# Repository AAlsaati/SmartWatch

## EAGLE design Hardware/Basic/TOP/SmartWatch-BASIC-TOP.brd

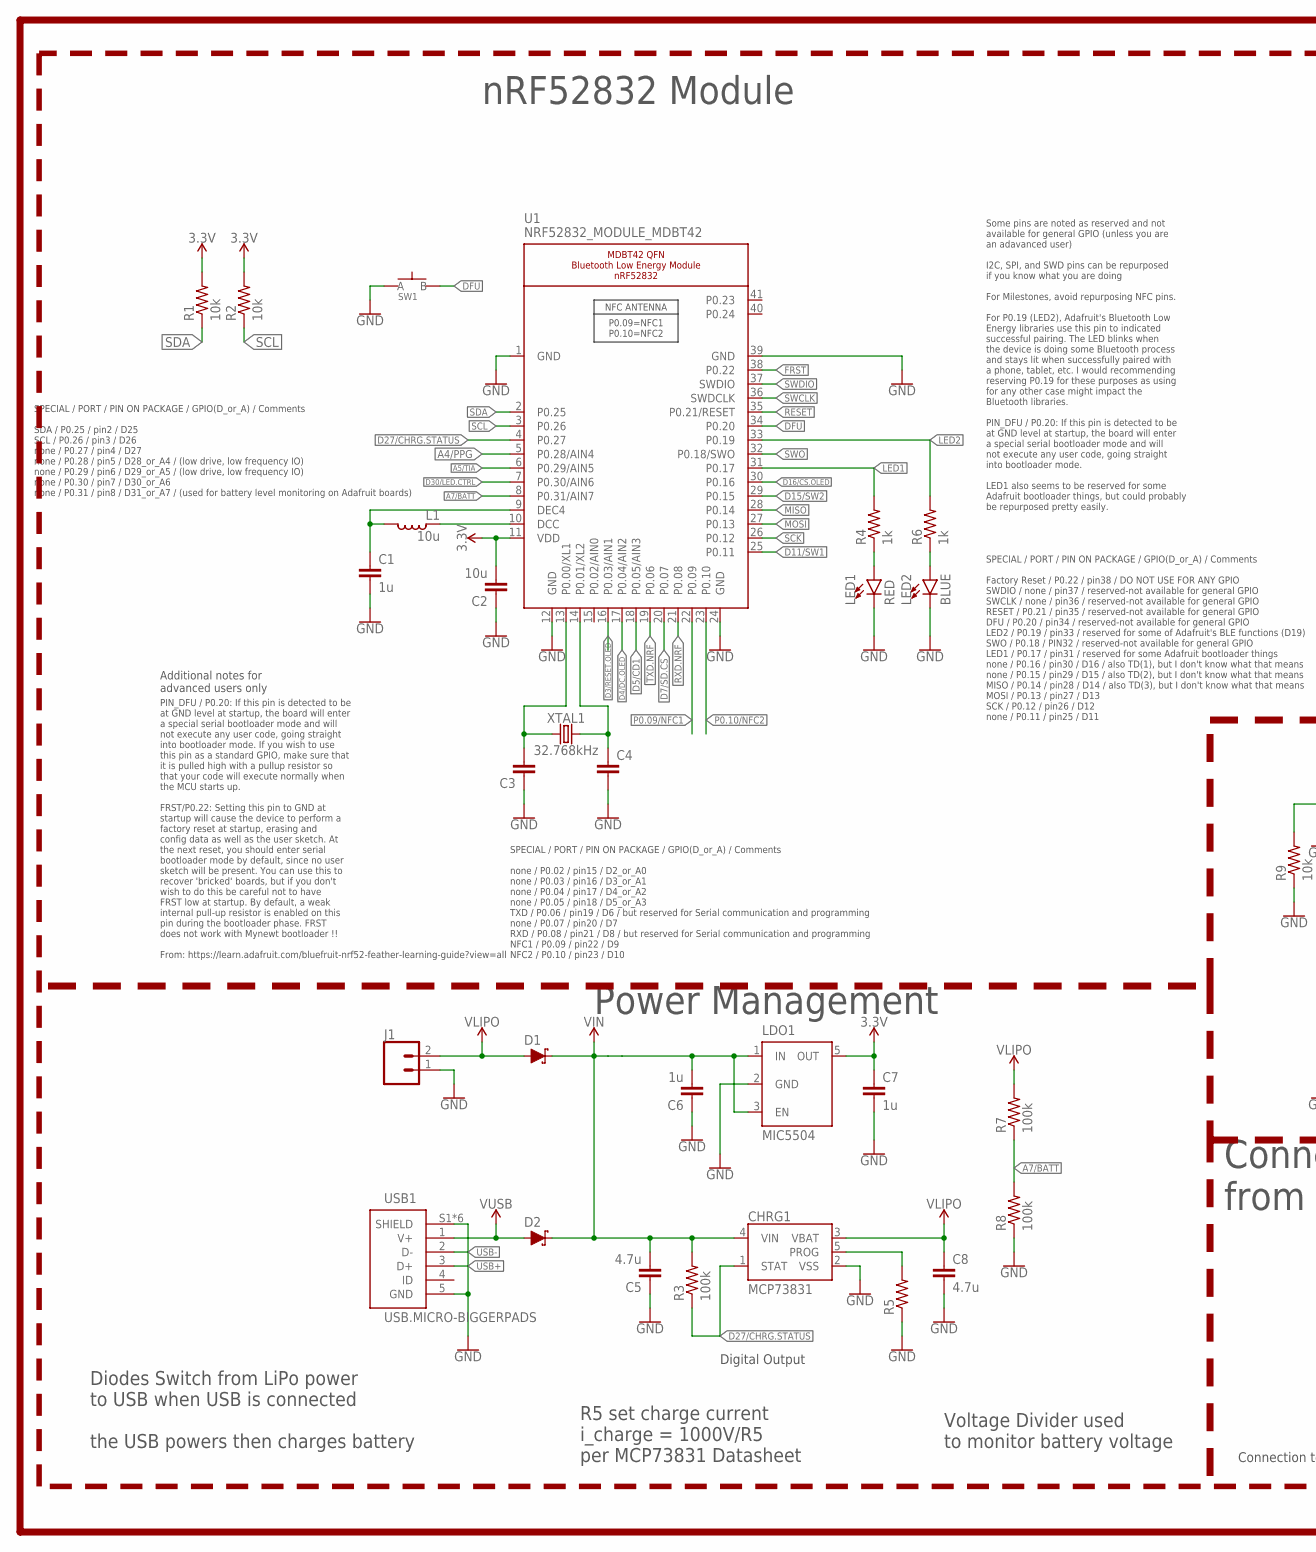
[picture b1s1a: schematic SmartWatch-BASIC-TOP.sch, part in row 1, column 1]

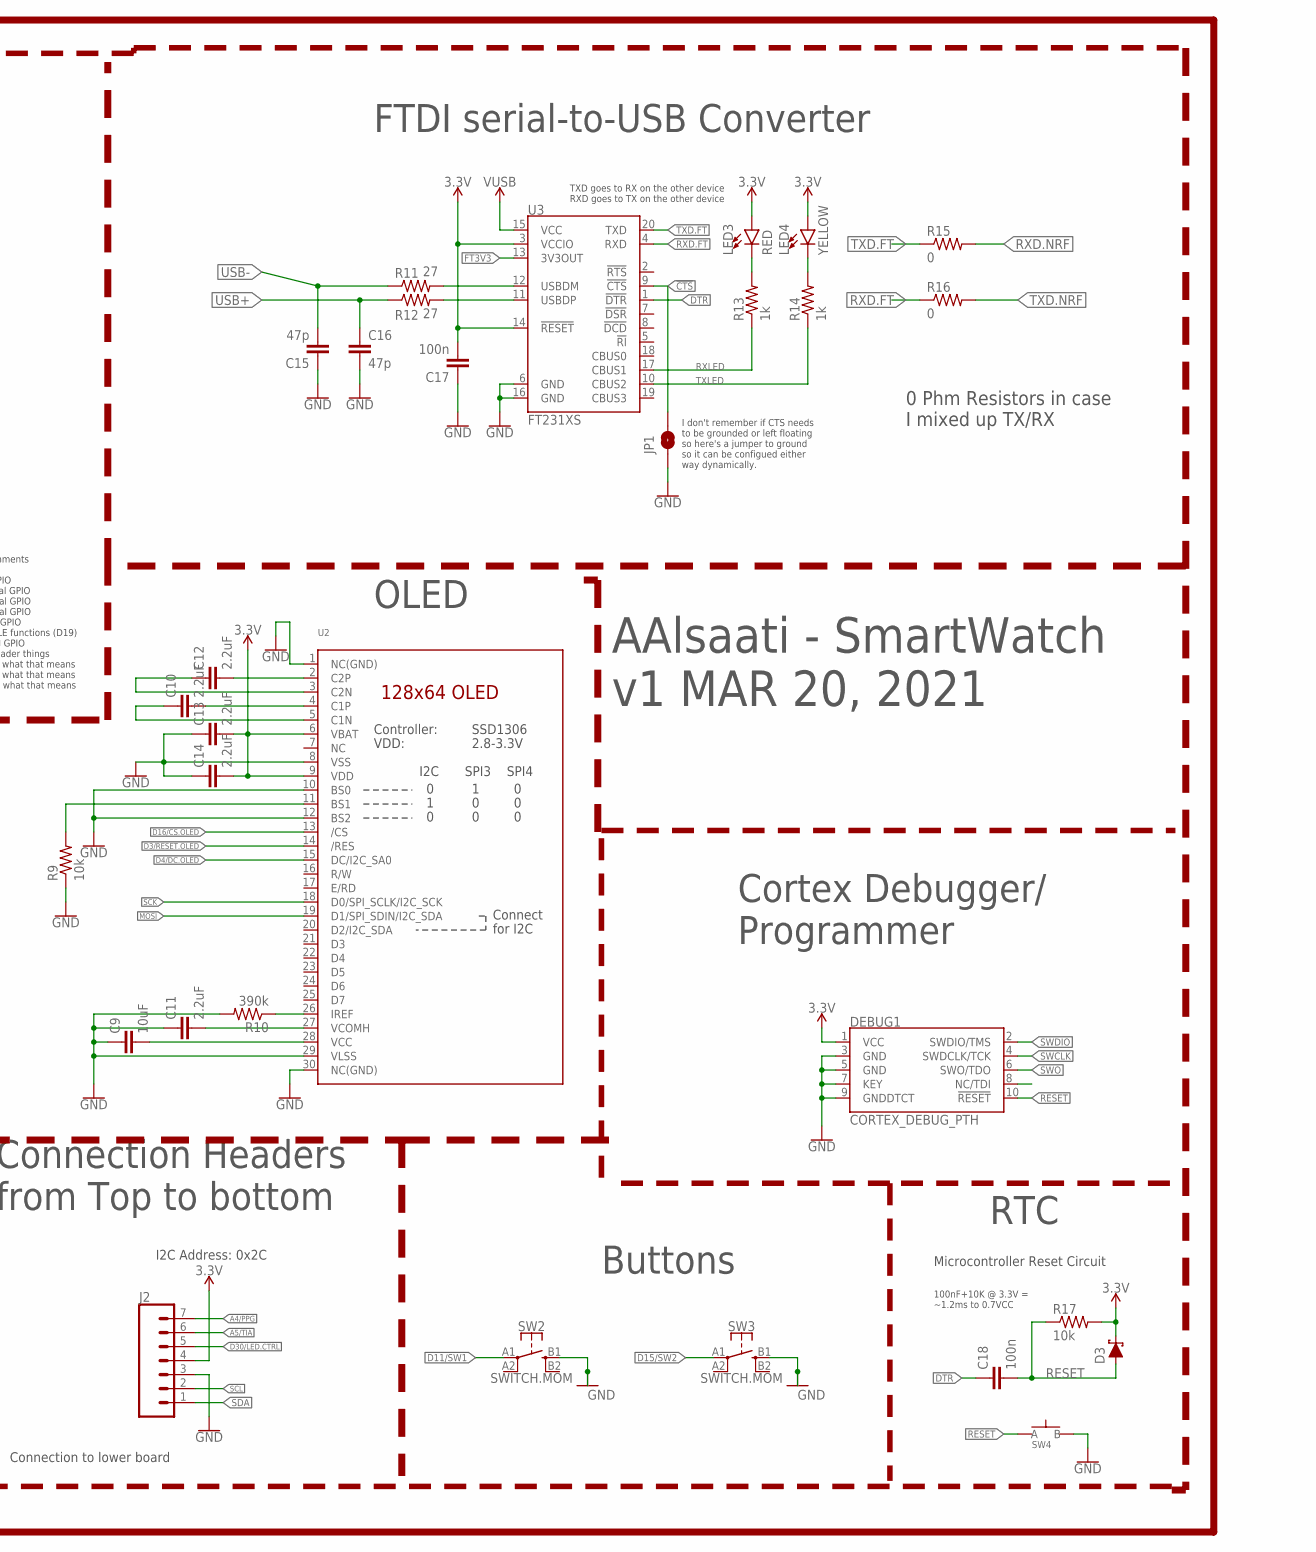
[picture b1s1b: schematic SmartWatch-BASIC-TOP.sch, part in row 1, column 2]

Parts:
C1, C6, C7: 1u; C0603
C2: 10u; C0805
C3, C4: CAPACITOR0603; C0603
C5, C8: 4.7u; C0603
C9: 10uF; C0603
C10, C12, C13, C14: 2.2uF; C0402
C11: 2.2uF; C0603
C15, C16: 47p; C0603
C17, C18: 100n; C0603
CHRG1: MCP73831; SOT23-5
D1, D2, D3: SCHOTTKY-USC; USC
DEBUG1: CORTEX_DEBUG_PTH; 2X5-PTH-1.27MM
J1: CONN_02; 1X02
J2: CONN_07-1.27MM; 1X07_1.27MM
JP1: JUMPER-SMT_2_NO_SILK; SMT-JUMPER_2_NO_SILK
L1: 10u; L0603
LDO1: MIC5504; SOT23-5
LED1, LED3: RED; LED-0603
LED2: BLUE; LED-0603
LED4: YELLOW; LED-0603
R1, R2, R9, R17: 10k; R0603
R3, R7, R8: 100k; R0603
R4, R6, R13, R14: 1k; R0603
R5: RESISTOR0603; R0603
R10: 390k; R0603
R11, R12: 27; R0603
R15, R16: 0; R0603
SW1, SW4: SPST-PTS830GG140-COPY.1-3; BUTTON-GULLWING
SW2, SW3: SWITCH.MOM; TACTILE_SWITCH_SMD_6.2MM_TALL
U1: NRF52832_MODULE_MDBT42; BLE_MODULE_RAYTAC_MDBT42
U2: DISP_OLED_UG-2864HSWEG01-NO-WRAPAROUND; UG-2864HSWEG01_0.96IN_NO-WRAPAROUND
U3: FT231XS; SSOP20_L
USB1: USB.MICRO-BIGGERPADS; USB-MICRO-01.BIGGERPADS
XTAL1: 32.768kHz; 2-SMD.NOLEAD.2.0MMTO1.2MM

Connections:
3.3V: C2.2, C7.1, C13.2, C14.2, C17.2, D3.- (C), DEBUG1.1 (VCC), J2.4, LDO1.5 (OUT), LED3.A, LED4.A, R1.2, R2.2, R17.2, U1.11 (VDD), U2.6 (VBAT), U2.9 (VDD), U3.3 (VCCIO), U3.14 (!RESET)
!CTS: JP1.2, U3.9 (!CTS)
A4/PPG: J2.7, U1.5 (P0.28/AIN4)
A5/TIA: J2.6, U1.6 (P0.29/AIN5)
A7/BATT: R7.1, R8.2, U1.8 (P0.31/AIN7)
D3/RESET.OLED: U1.16 (P0.03/AIN1), U2.14 (/RES)
D4/DC.OLED: U1.17 (P0.04/AIN2), U2.15 (DC/I2C_SA0)
D5/CD1: U1.18 (P0.05/AIN3)
D7/SD.CS: U1.20 (P0.07)
D11/SW1: SW2.A1 (1), U1.25 (P0.11)
D15/SW2: SW3.A1 (1), U1.29 (P0.15)
D16/CS.OLED: U1.30 (P0.16), U2.13 (/CS)
D27/CHRG.STATUS: CHRG1.1 (STAT), R3.1, U1.4 (P0.27)
D30/LED.CTRL: J2.5, U1.7 (P0.30/AIN6)
DFU: SW1.3 (B), U1.34 (P0.20)
DTR: C18.1, U3.1 (!DTR)
FRST: U1.38 (P0.22)
FT3V3: U3.13 (3V3OUT)
GND: C1.2, C2.1, C3.1, C4.2, C5.1, C6.1, C7.2, C8.2, C9.1, C11.1, C13.1, C14.1, C15.1, C16.2, C17.1, CHRG1.2 (VSS), DEBUG1.3 (GND), DEBUG1.5 (GND), DEBUG1.7 (KEY), DEBUG1.9 (GNDDTCT), J1.1, J2.3, JP1.1, LDO1.2 (GND), LED1.C, LED2.C, R5.1, R8.1, R9.1, R10.2, SW1.1 (A), SW2.B1 (3), SW3.B1 (3), SW4.3 (B), U1.1 (GND), U1.12 (GND), U1.24 (GND), U1.39 (GND), U2.1 (NC(GND)), U2.8 (VSS), U2.10 (BS0), U2.12 (BS2), U2.29 (VLSS), U2.30 (NC(GND)), U3.6 (GND), U3.16 (GND), USB1.5 (GND), USB1.S1 (SHIELD), USB1.S2 (SHIELD), USB1.S3 (SHIELD), USB1.S4 (SHIELD), USB1.S5 (SHIELD), USB1.S6 (SHIELD)
LED1: R4.2, U1.31 (P0.17)
LED2: R6.2, U1.33 (P0.19)
MISO: U1.28 (P0.14)
MOSI: U1.27 (P0.13), U2.19 (D1/SPI_SDIN/I2C_SDA)
unnamed: R9.2, U2.11 (BS1)
unnamed: R10.1, U2.26 (IREF)
unnamed: C12.2, U2.2 (C2P)
unnamed: C3.2, U1.13 (P0.00/XL1), XTAL1.P$1 (1)
unnamed: C12.1, U2.3 (C2N)
unnamed: C4.1, U1.14 (P0.01/XL2), XTAL1.P$2 (2)
unnamed: C10.2, U2.4 (C1P)
unnamed: C10.1, U2.5 (C1N)
unnamed: LED1.A, R4.1
unnamed: LED2.A, R6.1
unnamed: L1.1, U1.10 (DCC)
unnamed: C1.1, L1.2, U1.9 (DEC4)
unnamed: C9.2, U2.28 (VCC)
unnamed: C11.2, U2.27 (VCOMH)
unnamed: CHRG1.5 (PROG), R5.2
unnamed: R11.2, U3.12 (USBDM)
unnamed: R12.2, U3.11 (USBDP)
unnamed: LED3.C, R13.2
unnamed: LED4.C, R14.2
P0.09/NFC1: U1.22 (P0.09)
P0.10/NFC2: U1.23 (P0.10)
RESET: C18.2, D3.+ (A), DEBUG1.10 (!RESET), R17.1, SW4.1 (A), U1.35 (P0.21/RESET)
RXD.FT: R16.1, U3.4 (RXD)
RXD.NRF: R15.2, U1.21 (P0.08)
RXLED: R13.1, U3.17 (CBUS1)
SCK: U1.26 (P0.12), U2.18 (D0/SPI_SCLK/I2C_SCK)
SCL: J2.2, R2.1, U1.3 (P0.26)
SDA: J2.1, R1.1, U1.2 (P0.25)
SWCLK: DEBUG1.4 (SWDCLK/TCK), U1.36 (SWDCLK)
SWDIO: DEBUG1.2 (SWDIO/TMS), U1.37 (SWDIO)
SWO: DEBUG1.6 (SWO/TDO), U1.32 (P0.18/SWO)
TXD.FT: R15.1, U3.20 (TXD)
TXD.NRF: R16.2, U1.19 (P0.06)
TXLED: R14.1, U3.10 (CBUS2)
USB+: C16.1, R12.1, USB1.3 (D+)
USB-: C15.2, R11.1, USB1.2 (D-)
VIN: C5.2, C6.2, CHRG1.4 (VIN), D1.- (C), D2.- (C), LDO1.1 (IN), LDO1.3 (EN), R3.2
VLIPO: C8.1, CHRG1.3 (VBAT), D1.+ (A), J1.2, R7.2
V_USB: D2.+ (A), U3.15 (VCC), USB1.1 (V+)

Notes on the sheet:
Microcontroller Reset Circuit
100nF+10K @ 3.3V = ~1.2ms to 0.7VCC
SPECIAL / PORT / PIN ON PACKAGE / GPIO(D_or_A) / Comments SDA / P0.25 / pin2 / D25 SCL / P0.26 / pin3 / D26 none / P0.27 / pin4 / D27 none / P0.28 / pin5 / D28_or_A4 / (low drive, low frequency IO) none / P0.29 / pin6 / D29_or_A5 / (low drive, low frequency IO) none / P0.30 / pin7 / D30_or_A6 none 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
SPECIAL / PORT / PIN ON PACKAGE / GPIO(D_or_A) / Comments none / P0.02 / pin15 / D2_or_A0 none / P0.03 / pin16 / D3_or_A1 none / P0.04 / pin17 / D4_or_A2 none / P0.05 / pin18 / D5_or_A3 TXD / P0.06 / pin19 / D6 / but reserved for Serial communication and programming none / P0.07 / pin20 / D7 RXD / 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
SPECIAL / PORT / PIN ON PACKAGE / GPIO(D_or_A) / Comments Factory Reset / P0.22 / pin38 / DO NOT USE FOR ANY GPIO SWDIO / none / pin37 / reserved-not available for general GPIO SWCLK / none / pin36 / reserved-not available for general GPIO RESET / P0.21 / pin35 / reserved-not available for general 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
Some pins are noted as reserved and not available for general GPIO (unless you are an adavanced user) I2C, SPI, and SWD pins can be repurposed if you know what you are doing For Milestones, avoid repurposing NFC pins. For P0.19 (LED2), Adafruit's Bluetooth Low Energy libraries use this pin to indic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
PIN_DFU / P0.20: If this pin is detected to be at GND level at startup, the board will enter a special serial bootloader mode and will not execute any user code, going straight into bootloader mode. If you wish to use this pin as a standard GPIO, make sure that it is pulled high with a pullup resis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
Additional notes for advanced users only
nRF52832 Module
OLED
Power Management
Buttons
Cortex Debugger/ Programmer
RTC
TXD goes to RX on the other device RXD goes to TX on the other device
I don't remember if CTS needs to be grounded or left floating so here's a jumper to ground so it can be configued either way dynamically.
FTDI serial-to-USB Converter
I2C Address: 0x2C
Connection to lower board
Digital Output
AAlsaati - SmartWatch v1 MAR 20, 2021
Diodes Switch from LiPo power to USB when USB is connected the USB powers then charges battery
R5 set charge current i_charge = 1000V/R5 per MCP73831 Datasheet
Voltage Divider used to monitor battery voltage
Connection Headers from Top to bottom
0 Phm Resistors in case I mixed up TX/RX

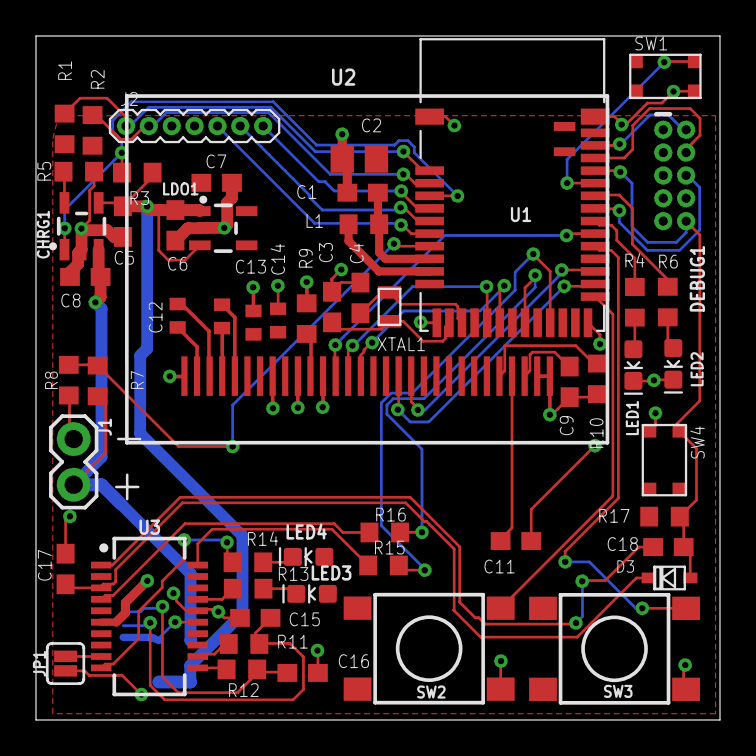
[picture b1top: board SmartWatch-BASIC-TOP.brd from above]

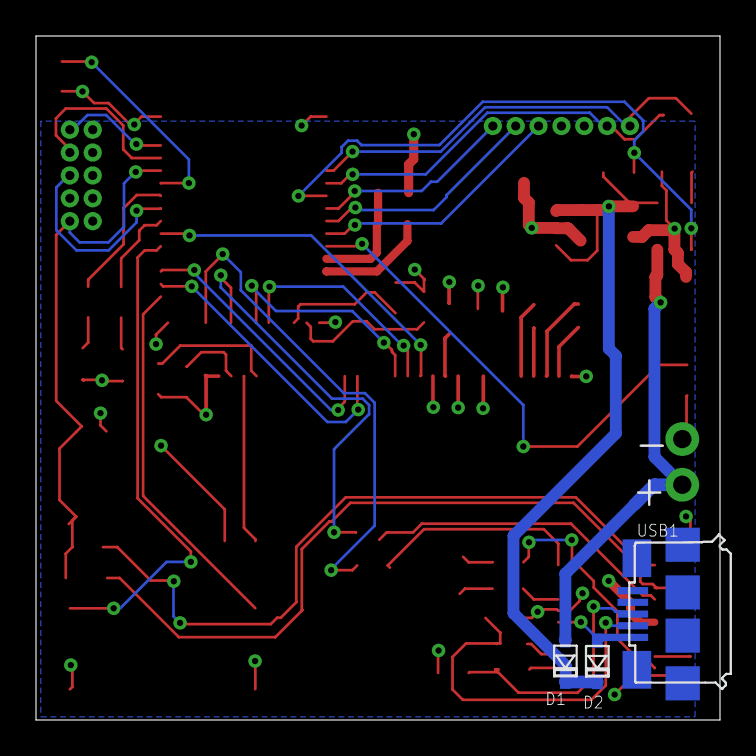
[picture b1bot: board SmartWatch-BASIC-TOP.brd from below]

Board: 2 copper layers, 38.0 x 38.0 mm, 58 parts (3 on the bottom side), 55 nets.

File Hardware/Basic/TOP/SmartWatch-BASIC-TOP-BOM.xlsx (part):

Design Name -- Revision Code / Designer or Organization Name |  |  |  |  |  |  |  |  |  |  | Total | 24.099299999999999 | Total (in Bulk) | 0
BOM # | Comment | Designator | Description | Mounting Type | Package | Manufacturer | Manufacturer Part Number | Supplier | Supplier Part Number | Price per unit | Quantity | Total | Per 100 | Total
Microcontroller
1 | NRF52832_MODULE_MDBT42 | U1 | Bluetooth Bluetooth v4.2 Transceiver Module 2.4GHz Integrated, Chip Surface Mou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 | SMD | 41-SMD Module | Seeed Technology Co., Ltd | 317030213 | Digi-Key | 1597-1434-ND | 10.1 | 1 | 10.1
2 | 10k Resistor | R1, R2, | 10 kOhms ±1% 0.1W, 1/10W Chip Resistor 0603 (1608 Metric) Automotive AEC-Q200 T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 | SMD | 0603 | Stackpole Electronics Inc | RMCF0603FT10K0 | Digi-Key | RMCF0603FT10K0CT-ND | 5.8999999999999999E-3 | 2 | 1.18E-2
3 | 1k Resistor | R4,R6 | 1 kOhms ±1% 0.1W, 1/10W Chip Resistor 0603 (1608 Metric) Automotive AEC-Q200 Th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 | SMD | 0603 | Stackpole Electronics Inc | RMCF0603FT1K00 | Digi-Key | RMCF0603FT1K00CT-ND | 5.8999999999999999E-3 | 2 | 1.18E-2
4 | Tiny Rectangular Switch | SW4 | Tactile Switch SPST-NO Top Actuated Surface Mount | SMD | Gull Wing | C&K Components | PTS830GM140 SMTR LFS | Digi-Key | CKN10587CT-ND | 0.56999999999999995 | 1 | 0.56999999999999995
5 | 10µH Inductor | L1 | 10µH Shielded Multilayer Inductor 250mA 1.05Ohm 0603 (1608 Metric) | SMD | 0603 | TDK Corporation | MLZ1608M100WTD25 | Digi-Key | MLZ1608M100WTD25 | 0.22 | 1 | 0.22
6 | 1uF capacitor | C1 | 1µF ±10% 25V Ceramic Capacitor X5R 0603 (1608 Metric) | SMD | 0603 | Samsung Electro-Mechanics | CL10A105KA8NNNC | Digi-Key | 1276-1102-1-ND | 0.1 | 1 | 0.1
7 | 10 uF 0603 Capacitor | C2 | 10µF ±10% 10V Ceramic Capacitor X5R 0603 (1608 Metric) | SMD | 0603 | Murata Electronics | GRM188R61A106KE69J | Digi-Key | 490-14372-1-ND | 6.3200000000000006E-2 | 1 | 6.3200000000000006E-2
8 | 12pF capacitor | C3, C4 | 12pF ±5% 50V Ceramic Capacitor C0G, NP0 0603 (1608 Metric) | SMD | 0603 | Walsin Technology Corporation | 0603N120J500CT | Digi-Key | 1292-1480-1-ND | 1.1900000000000001E-2 | 2 | 2.3800000000000002E-2
9 | Red LED | LED1 | Red 622nm LED Indication - Discrete 2.2V 0603 (1608 Metric) | SMD | 0603 | Inolux | IN-S63ATR | Digi-Key | 1830-1065-1-ND | 0.17699999999999999 | 1 | 0.17699999999999999
10 | Blue LED | LED2 | Blue 470nm LED Indication - Discrete 3V 0603 (1608 Metric) | SMD | 0603 | Inolux | IN-S63AT5B | Digi-Key | 1830-1061-1-ND | 0.17699999999999999 | 1 | 0.17699999999999999
11 | CRYSTALECS-.327-12.5-12-C-TR (CRYSTAL) (32.7680kHz) | XTAL1 | 32.768kHz ±10ppm Crystal 12.5pF 90 kOhms 2-SMD, No Lead | SMD | 2-SMD, No Lead | ECS Inc. | ECS-.327-12.5-12-C-TR | Digi-Key | XC2288CT-ND | 0.59799999999999998 | 1 | 0.59799999999999998
FTDI - USB |  |  |  |  |  |  |  |  |  |  |  | 0
12 | FT231XS USB Serial | U3 | USB Bridge, USB to UART USB 2.0 UART Interface 20-SSOP | SMD | 20-SSOP | FTDI, Future Technology Devices International Ltd | FT231XS-U | Digi-Key | 768-1156-5-ND | 2.12 | 1 | 2.12
13 | 47 pF Capacitor | C15, C16 | 47pF ±5% 50V Ceramic Capacitor C0G, NP0 0603 (1608 Metric) | SMD | 0603 | Walsin Technology Corporation | 0603N470J500CT | Digi-Key | 1292-1528-1-ND | 1.0999999999999999E-2 | 2 | 2.1999999999999999E-2
14 | 27 ohm resistor | R11, R12 | 27 Ohms ±1% 0.1W, 1/10W Chip Resistor 0603 (1608 Metric) Automotive AEC-Q200 Th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 | SMD | 0603 | Stackpole Electronics Inc | RMCF0603FT27R0 | Digi-Key | RMCF0603FT27R0CT-ND | 5.8999999999999999E-3 | 2 | 1.18E-2
15 | 100 nF Capacitor | C17 | 0.1µF ±5% 16V Ceramic Capacitor X7R 0603 (1608 Metric) | SMD | 0603 | Yageo | CC0603JRX7R7BB104 | Digi-Key | 311-1776-1-ND | 3.3099999999999997E-2 | 1 | 3.3099999999999997E-2
16 | 0 ohm resistor (not sure if needed) | JP1, R15, R16 | 0 Ohms Jumper 0.1W, 1/10W Chip Resistor 0603 (1608 Metric) Moisture Resistant T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 | SMD | 0603 | Yageo | RC0603JR-070RL | Digi-Key | 311-0.0GRCT-ND | 7.0000000000000001E-3 | 3 | 2.1000000000000001E-2
17 | 1k Resistor | R13,R14 | 1 kOhms ±1% 0.1W, 1/10W Chip Resistor 0603 (1608 Metric) Automotive AEC-Q200 Th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 | SMD | 0603 | Stackpole Electronics Inc | RMCF0603FT1K00 | Digi-Key | RMCF0603FT1K00CT-ND | 5.8999999999999999E-3 | 2 | 1.18E-2
18 | Red LED | LED3 | Red 622nm LED Indication - Discrete 2.2V 0603 (1608 Metric) | SMD | 0603 | Inolux | IN-S63ATR | Digi-Key | 1830-1065-1-ND | 0.17699999999999999 | 1 | 0.17699999999999999
19 | Yellow LED | LED4 | Yellow 590nm LED Indication - Discrete 2V 0603 (1608 Metric) | SMD | 0603 | Wurth Electronics Inc. | 150060YS75000 | Digi-Key | 732-4981-1-ND | 0.14000000000000001 | 1 | 0.14000000000000001
Debug |  |  |  |  |  |  |  |  |  |  |  | 0
20 | Cortex Debug Connector - 10 pin | DEBUG1 | Connector Header Through Hole 10 position 0.050" (1.27mm) | THT | NA | Amphenol ICC (FCI) | 20021111-00010T4LF | Digi-Key | 609-3712-ND | 0.69 | 1 | 0.69
RTC |  |  |  |  |  |  |  |  |  |  |  | 0
21 | 100 nF Capacitor | C18 | 0.1µF ±5% 16V Ceramic Capacitor X7R 0603 (1608 Metric) | SMD | 0603 | Yageo | CC0603JRX7R7BB104 | Digi-Key | 311-1776-1-ND | 3.3099999999999997E-2 | 1 | 3.3099999999999997E-2
22 | 10k Resistor | R17 | 10 kOhms ±1% 0.1W, 1/10W Chip Resistor 0603 (1608 Metric) Automotive AEC-Q200 T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 | SMD | 0603 | Stackpole Electronics Inc | RMCF0603FT10K0 | Digi-Key | RMCF0603FT10K0CT-ND | 5.8999999999999999E-3 | 1 | 5.8999999999999999E-3
23 | Schottky Diode | D3 | Diode Schottky 30V 1.5A Surface Mount USC | SMD | USC | Toshiba Semiconductor and Storage | CUS15S30,H3F | Digi-Key | CUS15S30H3FCT-ND | 0.25600000000000001 | 1 | 0.25600000000000001
24 | Tiny Rectangular Switch | SW4 | Tactile Switch SPST-NO Top Actuated Surface Mount | SMD | Gull Wing | C&K Components | PTS830GM140 SMTR LFS | Digi-Key | CKN10587CT-ND | 0.56999999999999995 | 1 | 0.56999999999999995
OLED |  |  |  |  |  |  |  |  |  |  |  | 0
25 | 0.96" OLED | OLED | Datasheet 128x64 OLED Module SPI 0.96"Graphic Displays,White on Black | SMD | Flexible Connector | EastRising | https://www.buydisplay.com/datasheet-128x64-oled-module-spi-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 | BuyDisplay.com | https://www.buydisplay.com/datasheet-128x64-oled-module-spi-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 | 2.5099999999999998 | 1 | 2.5099999999999998
26 | 10 uF 0603 Capacitor | C9 | 10µF ±10% 10V Ceramic Capacitor X5R 0603 (1608 Metric) | SMD | 0603 | Murata Electronics | GRM188R61A106KE69J | Digi-Key | 490-14372-1-ND | 6.3200000000000006E-2 |  | 0
27 | 2.2u capacitor | C10, C11, C12, C13, C14 | 2.2µF ±10% 16V Ceramic Capacitor X5R 0603 (1608 Metric) | SMD | 0603 | Samsung Electro-Mechanics | CL10A225KO8NNNC | Digi-Key | 1276-1040-1-ND | 3.1600000000000003E-2 | 5 | 0.15800000000000003
28 | 10k Resistor | R9 | 10 kOhms ±1% 0.1W, 1/10W Chip Resistor 0603 (1608 Metric) Automotive AEC-Q200 T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 | SMD | 0603 | Stackpole Electronics Inc | RMCF0603FT10K0 | Digi-Key | RMCF0603FT10K0CT-ND | 5.8999999999999999E-3 | 1 | 5.8999999999999999E-3
29 | 390k resistor | R10 | 390 kOhms ±1% 0.1W, 1/10W Chip Resistor 0603 (1608 Metric) Automotive AEC-Q200 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 | SMD | 0603 | Stackpole Electronics Inc | RMCF0603FG390K | Digi-Key | RMCF0603FG390KCT-ND | 5.8999999999999999E-3 | 1 | 5.8999999999999999E-3
Bottons |  |  |  |  |  |  |  |  |  |  |  | 0
30 | SWITCH.MOM (TACTILE_SWITCH_SMD_6.2MM_TALL) | SW2, SW3 | Tactile Switch SPST-NO Top Actuated Surface Mount - TACT 4.5 X 4.5, 5.0 MM H, 1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 | SMD | Gull Wing | C&K | PTS 647 SN50 SMTR2 LFS | Digi-Key | PTS647SN50SMTR2LFSCT-ND | 0.1208 | 2 | 0.24160000000000001
Connectors |  |  |  |  |  |  |  |  |  |  |  | 0
31 | CONN_07-1.27MM | J2 | 50 Positions Header Connector 0.050" (1.27mm) Through Hole Gold | THT |  | Sullins Connector Solutions | GRPB501VWVN-RC | Digi-Key | S9014E-50-ND | 3.11 | 1 | 3.11
Power |  |  |  |  |  |  |  |  |  |  |  | 0
32 | Micro USB | USB1 | USB - micro B USB 2.0 Receptacle Connector 5 Position Surface Mount, Right Angle | SMD | Flange, Horizontal | Amphenol FCI | 10118192-0001LF | Digi-Key | 609-4613-1-ND | 0.43 | 1 | 0.43
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
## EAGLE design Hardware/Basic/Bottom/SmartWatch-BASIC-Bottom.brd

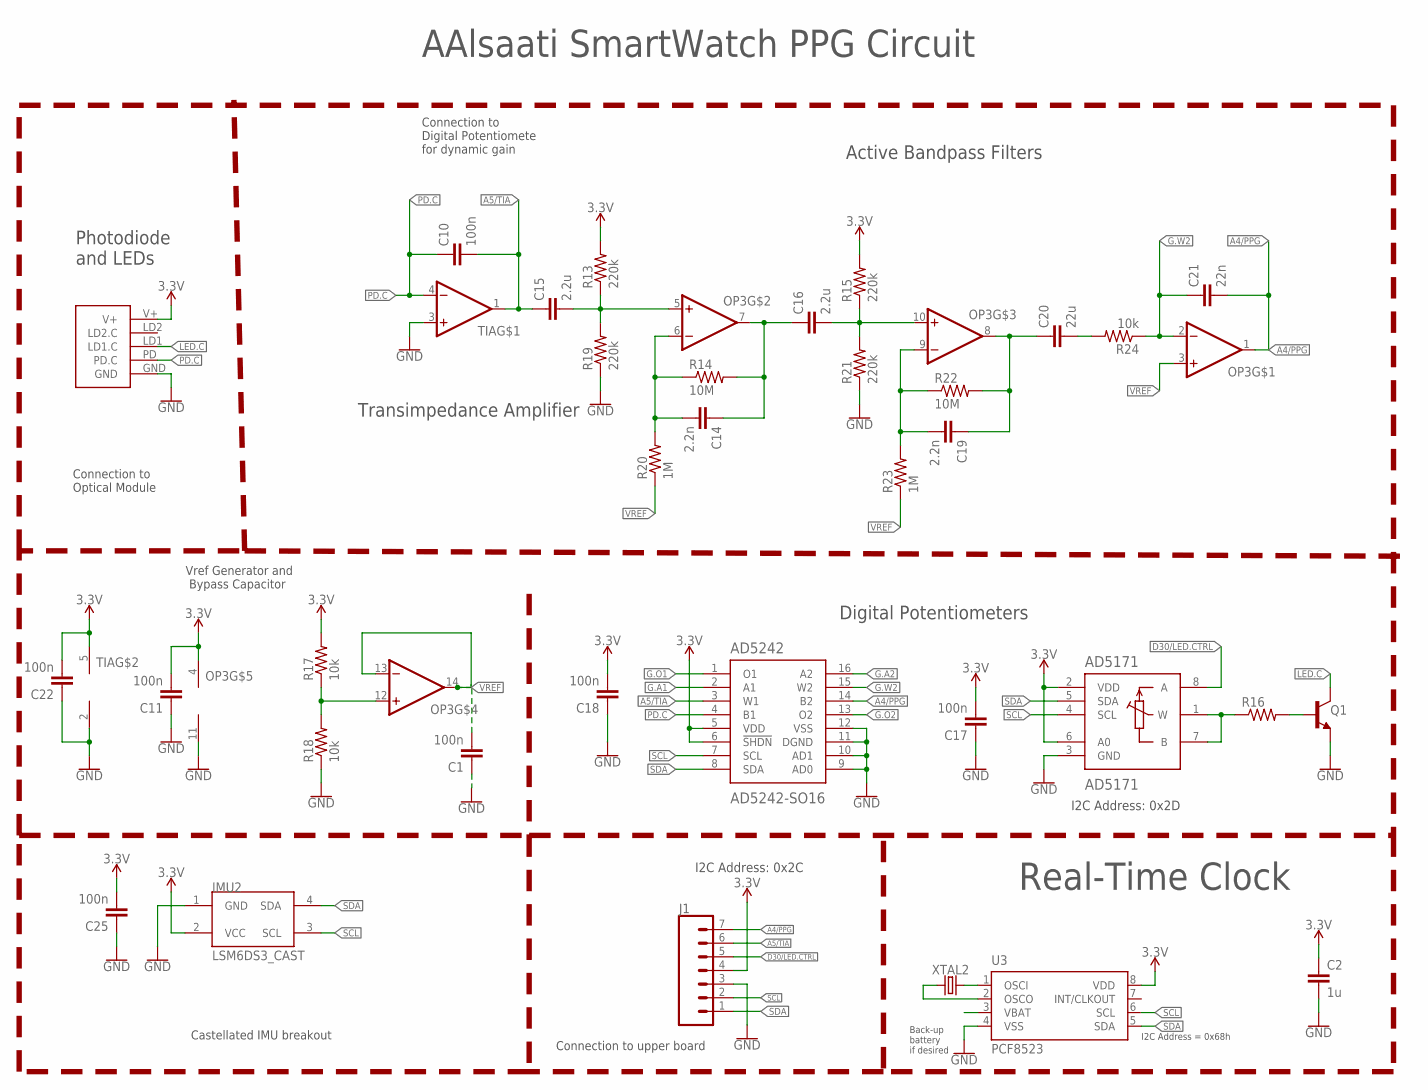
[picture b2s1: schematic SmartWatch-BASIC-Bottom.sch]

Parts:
AD5171: AD5171; SOT-23-8
AD5242: AD5242-SO16; SO16
C1, C10, C11, C17, C18, C22, C25: 100n; C0603
C2: 1u; C0603
C14, C19: 2.2n; C0603
C15, C16: 2.2u; C0603
C20: 22u; C0603
C21: 22n; C0603
IMU2: LSM6DS3_CAST
J1: CONN_07-1.27MM; 1X07_1.27MM
LOGO1: REVISION.A; REV.A
OP3: OP-QUAD-SO14; SO14
Q1: NPN-GENERIC; SOT23-3
R13, R15, R19, R21: 220k; R0603
R14, R22: 10M; R0603
R16: RESISTOR0603; R0603
R17, R18: 10k; R0402
R20, R23: 1M; R0603
R24: 10k; R0603
TIA: OP-SINGLEOT; SOT23-5
U3: PCF8523; SO8; DIGIKEY 568-5306-1-ND
U$3: PPG.MODULE.2
XTAL2: 32.7680kHz; 2-SMD.NOLEAD.2.0MMTO1.2MM

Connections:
3.3V: AD5171.2 (VDD), AD5171.6 (A0), AD5242.5 (VDD), AD5242.6 (!SHDN), C2.1, C11.2, C17.2, C18.2, C22.2, C25.2, IMU2.2 (VCC), J1.4, OP3.4 (V+), R13.2, R15.2, R17.2, TIA.5 (V+), U3.8 (VDD), U$3.V+
A4/PPG: AD5242.14 (B2), C21.2, J1.7, OP3.1 (OUT)
A5/TIA: AD5242.3 (W1), C10.2, C15.1, J1.6, TIA.1 (OUT)
D30/LED.CTRL: AD5171.8 (A), J1.5
G.A1: AD5242.2 (A1)
G.A2: AD5242.16 (A2)
G.O1: AD5242.1 (O1)
G.O2: AD5242.13 (O2)
G.W2: AD5242.15 (W2), C21.1, OP3.2 (-IN), R24.1
GND: AD5171.3 (GND), AD5242.9 (AD0), AD5242.10 (AD1), AD5242.11 (DGND), AD5242.12 (VSS), C1.1, C2.2, C11.1, C17.1, C18.1, C22.1, C25.1, IMU2.1 (GND), J1.3, OP3.11 (V-), Q1.2 (E), R18.1, R19.1, R21.1, TIA.2 (V-), TIA.3 (+IN), U3.4 (VSS), U$3.GND
LED.C: Q1.3 (C), U$3.LD1 (LD1.C)
unnamed: U3.2 (OSCO), XTAL2.P$1 (1)
unnamed: U3.1 (OSCI), XTAL2.P$2 (2)
unnamed: Q1.1 (B), R16.2
unnamed: AD5171.1 (W), AD5171.7 (B), R16.1
unnamed: OP3.12 (+IN), R17.1, R18.2
unnamed: C15.2, OP3.5 (+IN), R13.1, R19.2
unnamed: C14.2, OP3.6 (-IN), R14.1, R20.2
unnamed: C14.1, C16.1, OP3.7 (OUT), R14.2
unnamed: C16.2, OP3.10 (+IN), R15.1, R21.2
unnamed: C19.2, OP3.9 (-IN), R22.1, R23.2
unnamed: C19.1, C20.1, OP3.8 (OUT), R22.2
unnamed: C20.2, R24.2
PD.C: AD5242.4 (B1), C10.1, TIA.4 (-IN), U$3.PD (PD.C)
SCL: AD5171.4 (SCL), AD5242.7 (SCL), IMU2.3 (SCL), J1.2, U3.6 (SCL)
SDA: AD5171.5 (SDA), AD5242.8 (SDA), IMU2.4 (SDA), J1.1, U3.5 (SDA)
VBATT: U3.3 (VBAT)
VREF: C1.2, OP3.3 (+IN), OP3.13 (-IN), OP3.14 (OUT), R20.1, R23.1

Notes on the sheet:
Photodiode and LEDs
Active Bandpass Filters
Digital Potentiometers
Transimpedance Amplifier
I2C Address: 0x2C
I2C Address: 0x2D
Connection to Optical Module
Connection to Digital Potentiomete for dynamic gain
Connection to upper board
Castellated IMU breakout
Vref Generator and Bypass Capacitor
AAlsaati SmartWatch PPG Circuit
I2C Address = 0x68h
Back-up battery if desired
Real-Time Clock

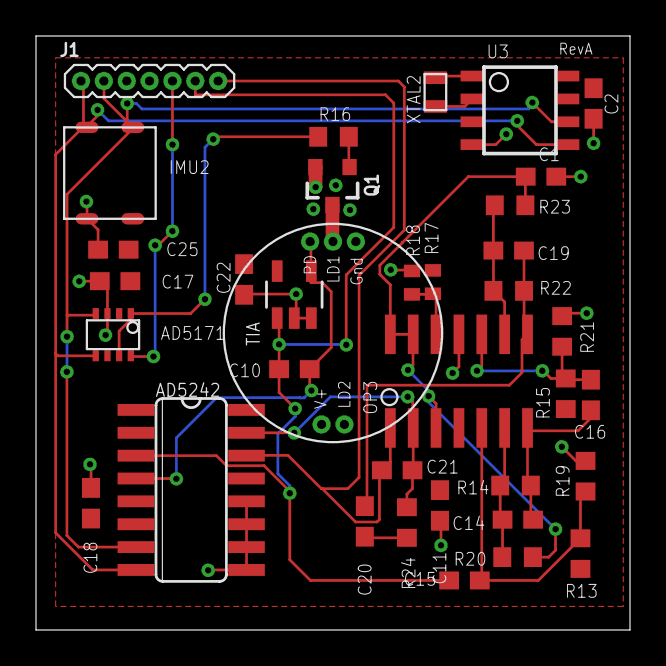
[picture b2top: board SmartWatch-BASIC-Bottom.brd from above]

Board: 2 copper layers, 33.0 x 33.0 mm, 37 parts (0 on the bottom side), 23 nets.

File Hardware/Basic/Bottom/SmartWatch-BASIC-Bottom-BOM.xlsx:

Design Name -- Revision Code / Designer or Organization Name |  |  |  |  |  |  |  |  |  |  | Total | 21.1187 | Total (in Bulk) | 0
BOM # | Comment | Designator | Description | Mounting Type | Package | Manufacturer | Manufacturer Part Number | Supplier | Supplier Part Number | Price per unit | Quantity | Total | Per 100 | Total
Filters
 | Op Amp - MCP6004 | OP3 | General Purpose Amplifier 4 Circuit Rail-to-Rail 14-SOIC | SMD | 14-SOIC | Microchip Technology | MCP6004T-I/SL | Digi-Key | MCP6004T-I/SLCT-ND | 0.44 | 6 | 2.64
 | 100 nF Capacitor | C10 | 0.1µF ±5% 16V Ceramic Capacitor X7R 0603 (1608 Metric) | SMD | 0603 | Yageo | CC0603JRX7R7BB104 | Digi-Key | 311-1776-1-ND | 3.3099999999999997E-2 | 1 | 3.3099999999999997E-2
 | 2.2u capacitor | C15, C16 | 2.2µF ±10% 16V Ceramic Capacitor X5R 0603 (1608 Metric) | SMD | 0603 | Samsung Electro-Mechanics | CL10A225KO8NNNC | Digi-Key | 1276-1040-1-ND | 3.1600000000000003E-2 | 2 | 6.3200000000000006E-2
 | 2.2n Capacitor | C14, C19 | 2200pF ±10% 50V Ceramic Capacitor X7R 0603 (1608 Metric) | SMD | 0603 | Walsin Technology Corporation | 0603B222K500CT | Digi-Key | 1292-1412-1-ND | 1.1599999999999999E-2 | 2 | 2.3199999999999998E-2
 | 22u capacitor | C20 | 22µF ±20% 10V Ceramic Capacitor X5R 0603 (1608 Metric) | SMD | 0603 | Samsung Electro-Mechanics | CL10A226MP8NUNE | Digi-Key | 1276-1274-1-ND | 6.7199999999999996E-2 | 1 | 6.7199999999999996E-2
 | 22n capacitor | C21 | 0.022µF ±10% 50V Ceramic Capacitor X7R 0603 (1608 Metric) | SMD | 0603 | Samsung Electro-Mechanics | CL10B223KB8NNNC | Digi-Key | 1276-1104-1-ND | 1.5599999999999999E-2 | 1 | 1.5599999999999999E-2
 | 220k resistor | R13, R19, R21, R15 | 220 kOhms ±1% 0.1W, 1/10W Chip Resistor 0603 (1608 Metric) Automotive AEC-Q200 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 | SMD | 0603 | Stackpole Electronics Inc | RMCF0603FT220K | Digi-Key | RMCF0603FT220KCT-ND | 5.8999999999999999E-3 | 4 | 2.3599999999999999E-2
 | 10M Resistor | R14,R22 | 10 MOhms ±1% 0.1W, 1/10W Chip Resistor 0603 (1608 Metric) Automotive AEC-Q200 T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 | SMD | 0603 | Stackpole Electronics Inc | RMCF0603FT10M0 | Digi-Key | RMCF0603FT10M0CT-ND | 8.8999999999999999E-3 | 2 | 1.78E-2
 | 1M Resistor | R20, R23 | 1 MOhms ±1% 0.1W, 1/10W Chip Resistor 0603 (1608 Metric) Automotive AEC-Q200 Th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 | SMD | 0603 | Stackpole Electronics Inc | RMCF0603FT1M00 | Digi-Key | RMCF0603FT1M00CT-ND | 5.8999999999999999E-3 | 2 | 1.18E-2
 | 10k Resistor | R24 | 10 kOhms ±1% 0.1W, 1/10W Chip Resistor 0603 (1608 Metric) Automotive AEC-Q200 T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 | SMD | 0603 | Stackpole Electronics Inc | RMCF0603FT10K0 | Digi-Key | RMCF0603FT10K0CT-ND | 5.8999999999999999E-3 | 1 | 5.8999999999999999E-3
 | 100 nF Capacitor | C22,C11,C1 | 0.1µF ±5% 16V Ceramic Capacitor X7R 0603 (1608 Metric) | SMD | 0603 | Yageo | CC0603JRX7R7BB104 | Digi-Key | 311-1776-1-ND | 3.3099999999999997E-2 | 100 | 3.3099999999999996
 | 10k Resistor | R17, R18 | 10 kOhms ±1% 0.1W, 1/10W Chip Resistor 0603 (1608 Metric) Automotive AEC-Q200 T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 | SMD | 0603 | Stackpole Electronics Inc | RMCF0603FT10K0 | Digi-Key | RMCF0603FT10K0CT-ND | 5.8999999999999999E-3 | 100 | 0.59
Pontentiometer
 | AD5242 | AD5242 | Digital Potentiometer 1M Ohm 2 Circuit 256 Taps I²C Interface 16-SOIC | SMD | 16-SOIC | Analog Devices Inc. | AD5242BRZ1M | Digi-Key | AD5242BRZ1M-ND | 3.47 | 1 | 3.47
 | AD5171 | AD5171 | Digital Potentiometer ICs IC 6-Bit OTP I2C | SMD | SOT-23-8 | Analog Devices | AD5171BRJZ100-R7 | Mouser | 584-AD5171BRJZ100-R7 | 2.68 | 1 | 2.68
 | 100 nF Capacitor | C17, C18 | 0.1µF ±5% 16V Ceramic Capacitor X7R 0603 (1608 Metric) | SMD | 0603 | Yageo | CC0603JRX7R7BB104 | Digi-Key | 311-1776-1-ND | 3.3099999999999997E-2 | 2 | 6.6199999999999995E-2
 |  | R16
 | NPN-Generic | Q1 | Bipolar (BJT) Transistor NPN 40V 600mA 300MHz 250mW Surface Mount TO-236AB | SMD | TO-236AB | Nexperia USA Inc. | PMBT2222A,215 | Digi-Key | 1727-2956-1-ND | 1.05 | 1 | 1.05
IMU
 | LSM6DS3 castellated breakout
 | 100 nF Capacitor | C25 | 0.1µF ±5% 16V Ceramic Capacitor X7R 0603 (1608 Metric) | SMD | 0603 | Yageo | CC0603JRX7R7BB104 | Digi-Key | 311-1776-1-ND | 3.3099999999999997E-2 | 1 | 3.3099999999999997E-2
 | CONN_07-1.27MM (CONN_07) |  | 50 Position Header Connector 0.050" (1.27mm) Through Hole Gold | THT |  | Sullins Connector Solutions | LPPB501NFFN-RC | Digi-Key | S9008E-50-ND | 5.0599999999999996 | 1 | 5.0599999999999996
RTC
 | PCF8523 | U3 | Real Time Clock (RTC) IC Clock/Calendar I²C, 2-Wire Serial 8-SOIC (0.154", 3.90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 | SMD | 8-SO | NXP USA Inc. | PCF8523T/1,118 | Digi-Key | 568-5306-1-ND | 1.26 | 1 | 1.26
 | 1uF capacitor | C2 | 1µF ±10% 25V Ceramic Capacitor X5R 0603 (1608 Metric) | SMD | 0603 | Samsung Electro-Mechanics | CL10A105KA8NNNC | Digi-Key | 1276-1102-1-ND | 0.1 | 1 | 0.1
 | CRYSTALECS-.327-12.5-12-C-TR (CRYSTAL) (32.7680kHz) | XTAL2 | 32.768kHz ±10ppm Crystal 12.5pF 90 kOhms 2-SMD, No Lead | SMD | 2-SMD, No Lead | ECS Inc. | ECS-.327-12.5-12-C-TR | Digi-Key | XC2288CT-ND | 0.59799999999999998 | 1 | 0.59799999999999998

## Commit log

2021-02-06 Word Document
2021-02-06 Oraganizing-SmartWatch
2021-02-13 TopBoard
2021-02-27 Bottom Board
2021-02-28 take 2
2021-03-06 take3
2021-03-07 take3_1_24
2021-03-08 Take5
2021-03-10 take6
2021-03-13 take7
2021-03-14 take 8
2021-03-14 take8
2021-03-20 'take8'
2021-03-20 'PPG-Module'
